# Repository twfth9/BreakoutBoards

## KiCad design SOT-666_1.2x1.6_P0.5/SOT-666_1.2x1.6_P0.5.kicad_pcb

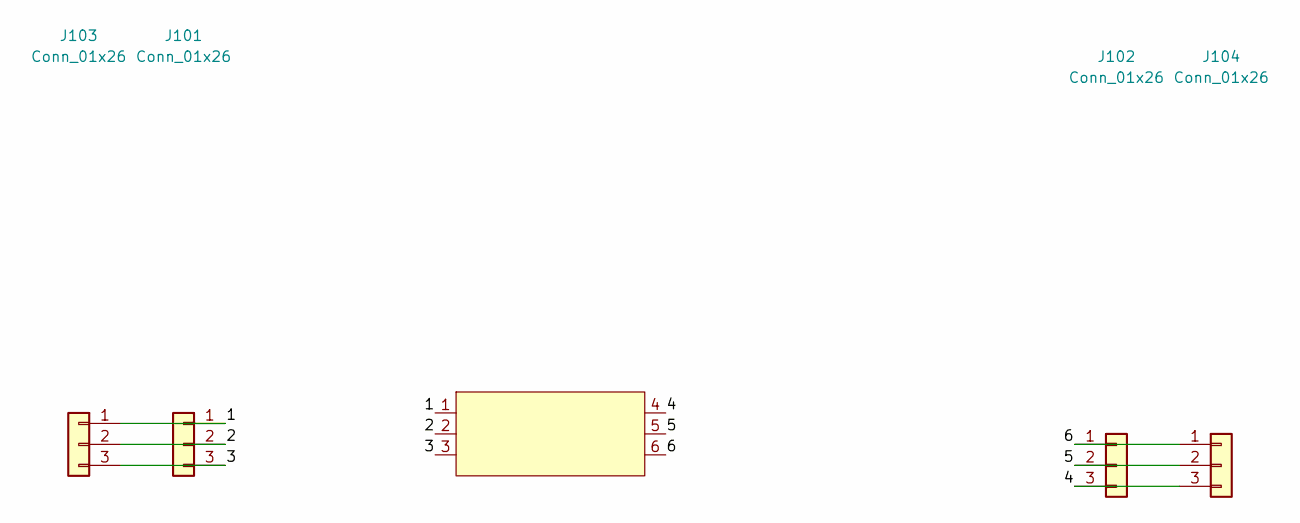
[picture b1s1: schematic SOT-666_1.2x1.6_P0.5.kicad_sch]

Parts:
J101, J102: Conn_01x26; PinHeader_1x03_P2.54mm_Vertical
J103, J104: Conn_01x26; PinHeader_1x03_P2.54mm_Vertical_SMD_Pin1Right
U101: SOT-666

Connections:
/1: J101.1, J103.1, U101.1
/2: J101.2, J103.2, U101.2
/3: J101.3, J103.3, U101.3
/4: J102.3, J104.3, U101.4
/5: J102.2, J104.2, U101.5
/6: J102.1, J104.1, U101.6

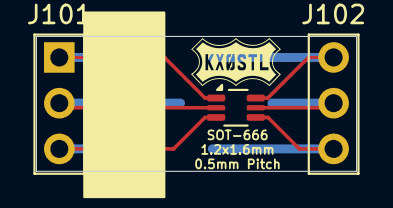
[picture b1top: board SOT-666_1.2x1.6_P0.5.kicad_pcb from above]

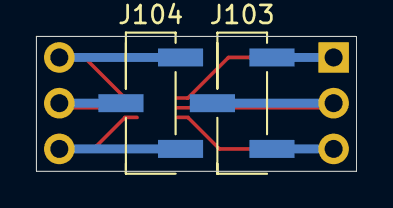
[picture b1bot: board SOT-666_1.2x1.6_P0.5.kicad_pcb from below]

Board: 2 copper layers, 17.8 x 7.5 mm, 5 parts (2 on the bottom side), 6 nets.

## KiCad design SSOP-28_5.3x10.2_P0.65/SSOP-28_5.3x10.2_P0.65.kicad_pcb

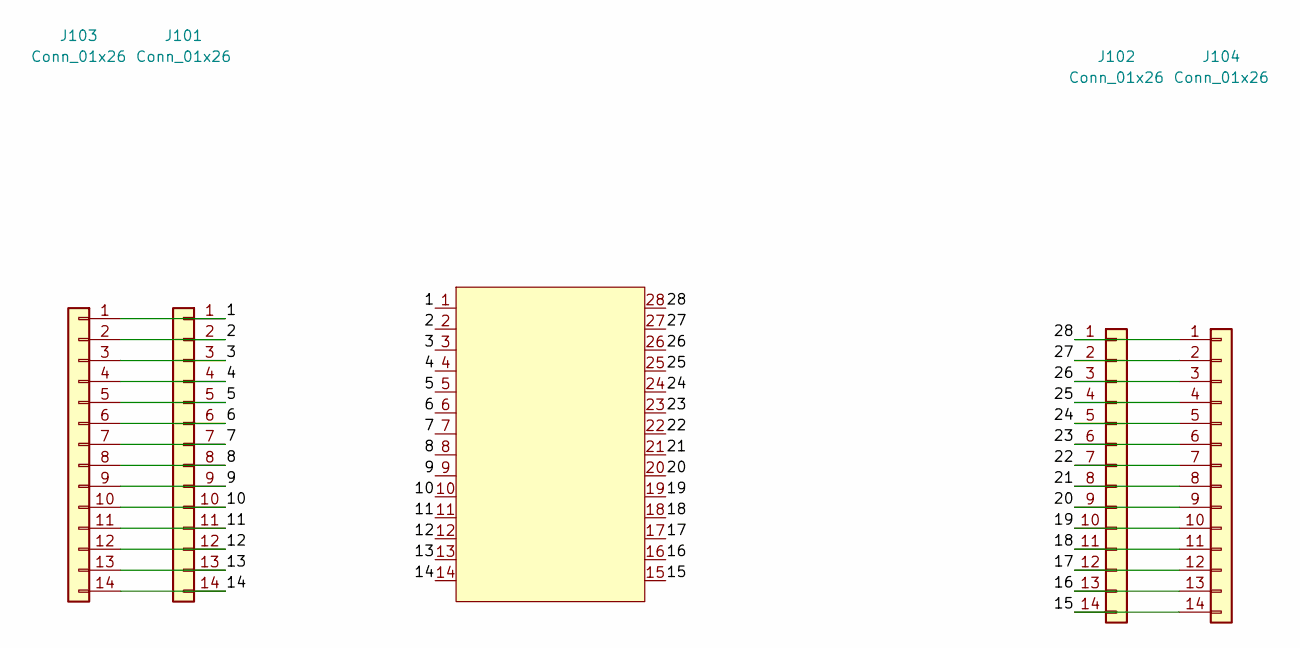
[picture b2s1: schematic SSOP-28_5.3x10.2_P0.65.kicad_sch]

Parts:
J101, J102: Conn_01x26; PinHeader_1x14_P2.54mm_Vertical
J103, J104: Conn_01x26; PinHeader_1x14_P2.54mm_Vertical_SMD_Pin1Right
U101: SSOP-28; SSOP-28_5.3x10.2mm_P0.65mm

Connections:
/1: J101.1, J103.1, U101.1
/2: J101.2, J103.2, U101.2
/3: J101.3, J103.3, U101.3
/4: J101.4, J103.4, U101.4
/5: J101.5, J103.5, U101.5
/6: J101.6, J103.6, U101.6
/7: J101.7, J103.7, U101.7
/8: J101.8, J103.8, U101.8
/9: J101.9, J103.9, U101.9
/10: J101.10, J103.10, U101.10
/11: J101.11, J103.11, U101.11
/12: J101.12, J103.12, U101.12
/13: J101.13, J103.13, U101.13
/14: J101.14, J103.14, U101.14
/15: J102.14, J104.14, U101.15
/16: J102.13, J104.13, U101.16
/17: J102.12, J104.12, U101.17
/18: J102.11, J104.11, U101.18
/19: J102.10, J104.10, U101.19
/20: J102.9, J104.9, U101.20
/21: J102.8, J104.8, U101.21
/22: J102.7, J104.7, U101.22
/23: J102.6, J104.6, U101.23
/24: J102.5, J104.5, U101.24
/25: J102.4, J104.4, U101.25
/26: J102.3, J104.3, U101.26
/27: J102.2, J104.2, U101.27
/28: J102.1, J104.1, U101.28

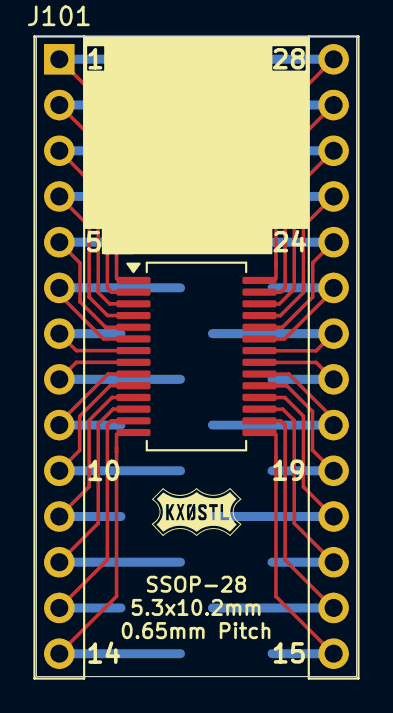
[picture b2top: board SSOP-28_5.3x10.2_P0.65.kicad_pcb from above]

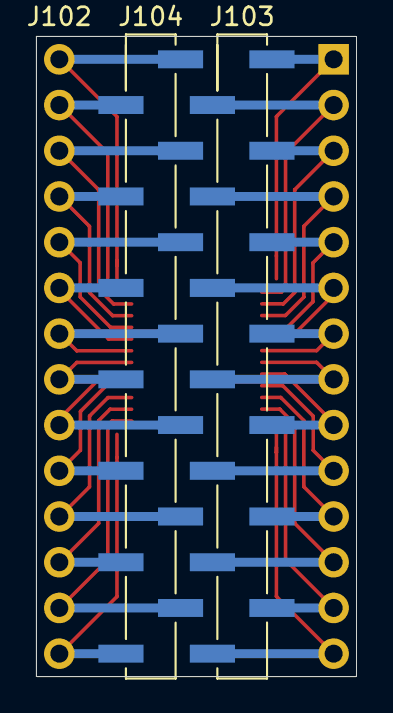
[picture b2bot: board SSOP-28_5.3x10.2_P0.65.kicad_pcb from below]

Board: 2 copper layers, 17.8 x 35.6 mm, 5 parts (3 on the bottom side), 28 nets.
